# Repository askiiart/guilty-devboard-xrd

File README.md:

# Guilty Devboard Xrd

A dev board for my keyboard, because all the other options kinda suck(ed)

- Compatible with both XIAO nRF52840 Plus and nRF54LM20A
- As efficient as possible
- Fast battery charging (configurable ~50-700mA) and over(dis)charge protection
- Up to 5V 3A from USB, and 3.3V 1A (including MCU power draw)
- 27 GPIO pins, nearly as much as the XIAO nRF54LM20A, despite much more limited manufacturing capabilities, while still having an antenna built-in.

See the documentation for more details on what this has over the official XIAOs.

## Documentation

Docs are available [here](https://askiiart.net/docs/guilty-devboard-xrd.html) ([short link](http://7qq.uk/xrd))

## Note: DRC errors

DRC shows ~140 clearance errors due to the Xiao Plus footprint having pads at and past the edge of the board, a couple things in the keep-out zone, and the QR codes overlapping/being too close to other items. That's intentional, ignore those.

## Schematic

Use Kicanvas to see the [schematic](https://kicanvas.org/?repo=https%3A%2F%2Fgithub.com%2Faskiiart%2Fguilty-devboard-idk%2Fblob%2Fmain%2FPCB%2Fguilty-devboard-idk.kicad_sch)

## Bill of Materials

| Name                           | Quantity needed | MOQ | Price  | Quantity to order | Link                                                                                                              | Total     |
| ------------------------------ | --------------- | --- | ------ | ----------------- | ----------------------------------------------------------------------------------------------------------------- | --------- |
| Diodes                         | 2               | 20  | 0.0257 | 20                | <https://www.lcsc.com/product-detail/C2912031.html>                                                               | 0.514     |
| Ferrite bead                   | 2               | 50  | 0.025  | 50                | <https://www.lcsc.com/product-detail/C525479.html>                                                                | 1.25      |
| MOSFETs                        | 1               | 10  | 0.0434 | 10                | <https://www.lcsc.com/product-detail/C41355091.html>                                                              | 0.434     |
| 100nF cap                      | 5               | 50  | 0.0018 | 50                | <https://www.lcsc.com/product-detail/C2903664.html>                                                               | 0.09      |
| 4.7uF cap                      | 4               | 10  | 0.0733 | 10                | <https://www.lcsc.com/product-detail/C335103.html>                                                                | 0.733     |
| 1pF cap                        | 1               | 100 | 0.0024 | 100               | <https://www.lcsc.com/product-detail/C85894.html>                                                                 | 0.24      |
| 2.2uF cap                      | 2               | 50  | 0.0346 | 50                | <https://www.lcsc.com/product-detail/C335106.html>                                                                | 1.73      |
| 10uF cap                       | 1               | 20  | 0.0368 | 20                | <https://www.lcsc.com/product-detail/C76991.html>                                                                 | 0.736     |
| 1.5pF cap                      | 1               | 100 | 0.003  | 100               | <https://www.lcsc.com/product-detail/C284990.html>                                                                | 0.3       |
| 22uF cap                       | 2               | 5   | 0.1522 | 5                 | <https://www.lcsc.com/product-detail/C7432764.html>                                                               | 0.761     |
| 470nF cap                      | 1               | 100 | 0.0057 | 100               | <https://www.lcsc.com/product-detail/C326573.html>                                                                | 0.57      |
| 1.2pF cap                      | 1               | 100 | 0.0016 | 100               | <https://www.lcsc.com/product-detail/C22374839.html>                                                              | 0.16      |
| 3.3nF inductor                 | 1               | 100 | 0.0073 | 100               | <https://www.lcsc.com/product-detail/C98045.html>                                                                 | 0.73      |
| 1.5uH inductor                 | 1               | 50  | 0.0111 | 50                | <https://www.lcsc.com/product-detail/C2885839.html>                                                               | 0.555     |
| 4.7nH inductor                 | 1               | 100 | 0.0099 | 100               | <https://www.lcsc.com/product-detail/C86126.html>                                                                 | 0.99      |
| 3.6nH inductor                 | 1               | 20  | 0.0322 | 20                | <https://www.lcsc.com/product-detail/C237447.html>                                                                | 0.644     |
| 4.7uH inductor                 | 1               | 1   | 0.2829 | 1                 | <https://www.lcsc.com/product-detail/C7261423.html>                                                               | 0.2829    |
| 1nH inductor                   | 1               | 100 | 0.0029 | 100               | <https://www.lcsc.com/product-detail/C46607389.html>                                                              | 0.29      |
| 5.1k resistor                  | 2               | 100 | 0.0007 | 100               | <https://www.lcsc.com/product-detail/C473460.html>                                                                | 0.07      |
| 470k resistor                  | 1               | 100 | 0.0013 | 100               | <https://www.lcsc.com/product-detail/C54530578.html>                                                              | 0.13      |
| 30 ohm resistor                | 2               | 100 | 0.0008 | 100               | <https://www.lcsc.com/product-detail/C320826.html>                                                                | 0.08      |
| 2k resistor                    | 1               | 100 | 0.0021 | 100               | <https://www.lcsc.com/product-detail/C138107.html>                                                                | 0.21      |
| 1k resistor                    | 1               | 100 | 0.001  | 100               | <https://www.lcsc.com/product-detail/C131396.html>                                                                | 0.1       |
| 806k resistor                  | 1               | 100 | 0.0009 | 100               | <https://www.lcsc.com/product-detail/C474840.html>                                                                | 0.09      |
| 2M resistor                    | 1               | 100 | 0.0006 | 100               | <https://www.lcsc.com/product-detail/C138106.html>                                                                | 0.06      |
| 10k resistor                   | 1               | 100 | 0.001  | 100               | <https://www.lcsc.com/product-detail/C138117.html>                                                                | 0.1       |
| 220k resistor                  | 1               | 100 | 0.003  | 100               | <https://www.lcsc.com/product-detail/C142020.html>                                                                | 0.3       |
| 68k resistor                   | 1               | 100 | 0.003  | 100               | <https://www.lcsc.com/product-detail/C274345.html>                                                                | 0.3       |
| 2.2 ohm resistor               | 1               | 100 | 0.0037 | 100               | <https://www.lcsc.com/product-detail/C473517.html>                                                                | 0.37      |
| 200 ohm resistor               | 1               | 100 | 0.0011 | 100               | <https://www.lcsc.com/product-detail/C304517.html>                                                                | 0.11      |
| SGM40567                       | 1               | 1   | 0.53   | 1                 | <https://www.lcsc.com/product-detail/C5141336.html>                                                               | 0.53      |
| FH9261-G3JH                    | 1               | 20  | 0.0289 | 20                | <https://www.lcsc.com/product-detail/C19273258.html>                                                              | 0.578     |
| BD83070GWL-E2                  | 1               | 1   | 0.7198 | 1                 | <https://www.lcsc.com/product-detail/C2071126.html>                                                               | 0.7198    |
| 32MHz crystal                  | 1               | 5   | 1.0134 | 1                 | <https://www.lcsc.com/product-detail/C5203637.html>                                                               | 1.0134    |
| 32.768kHz crystal              | 1               | 1   | 3.0197 | 1                 | <https://www.lcsc.com/product-detail/C2595065.html>                                                               | 3.0197    |
|                                |                 |     |        |                   |                                                                                                                   |           |
| 2450AT18D0100001E              | 1               | 1   | 0.57   | 1                 | <https://www.digikey.com/en/products/detail/johanson-technology-inc/2450AT18D0100001E/4770685>                    | 0.57      |
|                                |                 |     |        |                   |                                                                                                                   |           |
| NRF54LM20A-QGAA-R              | 1               | 1   | 6.7    | 1                 | <https://mou.sr/44t4RAm>                                                                                          | 6.7       |
| Amphenol 124019772112A (USB-C) | 1               | 1   | 2.41   | 1                 | <https://www.mouser.com/ProductDetail/Amphenol-Commercial-Products/124019772112A?qs=OlC7AqGiEDmvQ2B4jeqfyg%3D%3D> | 2.41      |
|                                |                 |     |        |                   |                                                                                                                   |           |
| JLCPCB                         |                 |     |        |                   |                                                                                                                   | $15.10    |
|                                |                 |     |        |                   |                                                                                                                   |           |
| JLCPCB shipping                |                 |     |        |                   | Roughly                                                                                                           | $9.79     |
| Digikey shipping               |                 |     |        |                   |                                                                                                                   | $4.99     |
| LCSC shipping                  |                 |     |        |                   |                                                                                                                   | 7.25      |
| Mouser shipping                |                 |     |        |                   |                                                                                                                   | 8.49      |
| Mouser estimated tariffs       |                 |     |        |                   |                                                                                                                   | 0.24      |
|                                |                 |     |        |                   |                                                                                                                   |           |
| Subtotal                       |                 |     |        |                   |                                                                                                                   | 74.3308   |
| Total                          |                 |     |        |                   |                                                                                                                   | 80.463091 |

## Notes

- The layer stackup should be JLC0616H-3313, and a stencil with electropolishing is recommended.
- The choice of USB-C connector is odd due to space requirements. If you can find a USB-C connector with the same footprint or smaller - at least in depth - then *please* tell me.
- Kicad, [marbastlib](https://github.com/ebastler/marbastlib), and [nordic-lib-kicad](https://github.com/hlord2000/nordic-lib-kicad) are required for this project.

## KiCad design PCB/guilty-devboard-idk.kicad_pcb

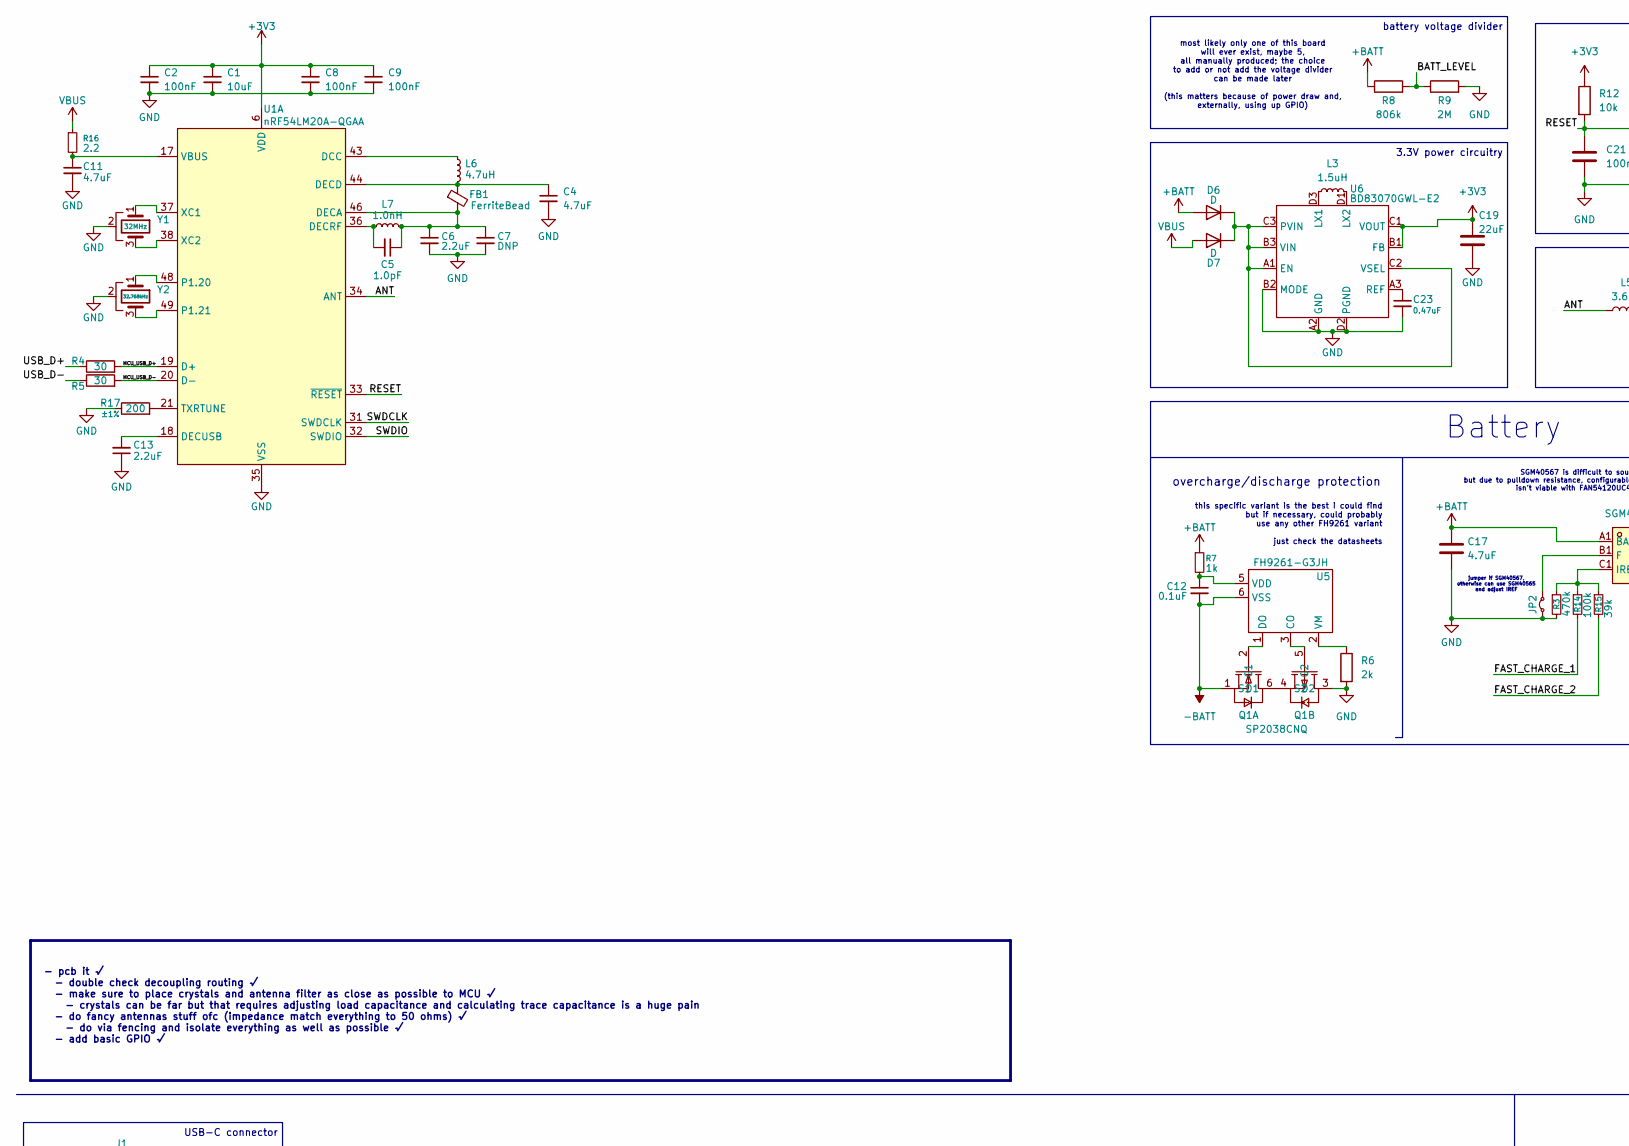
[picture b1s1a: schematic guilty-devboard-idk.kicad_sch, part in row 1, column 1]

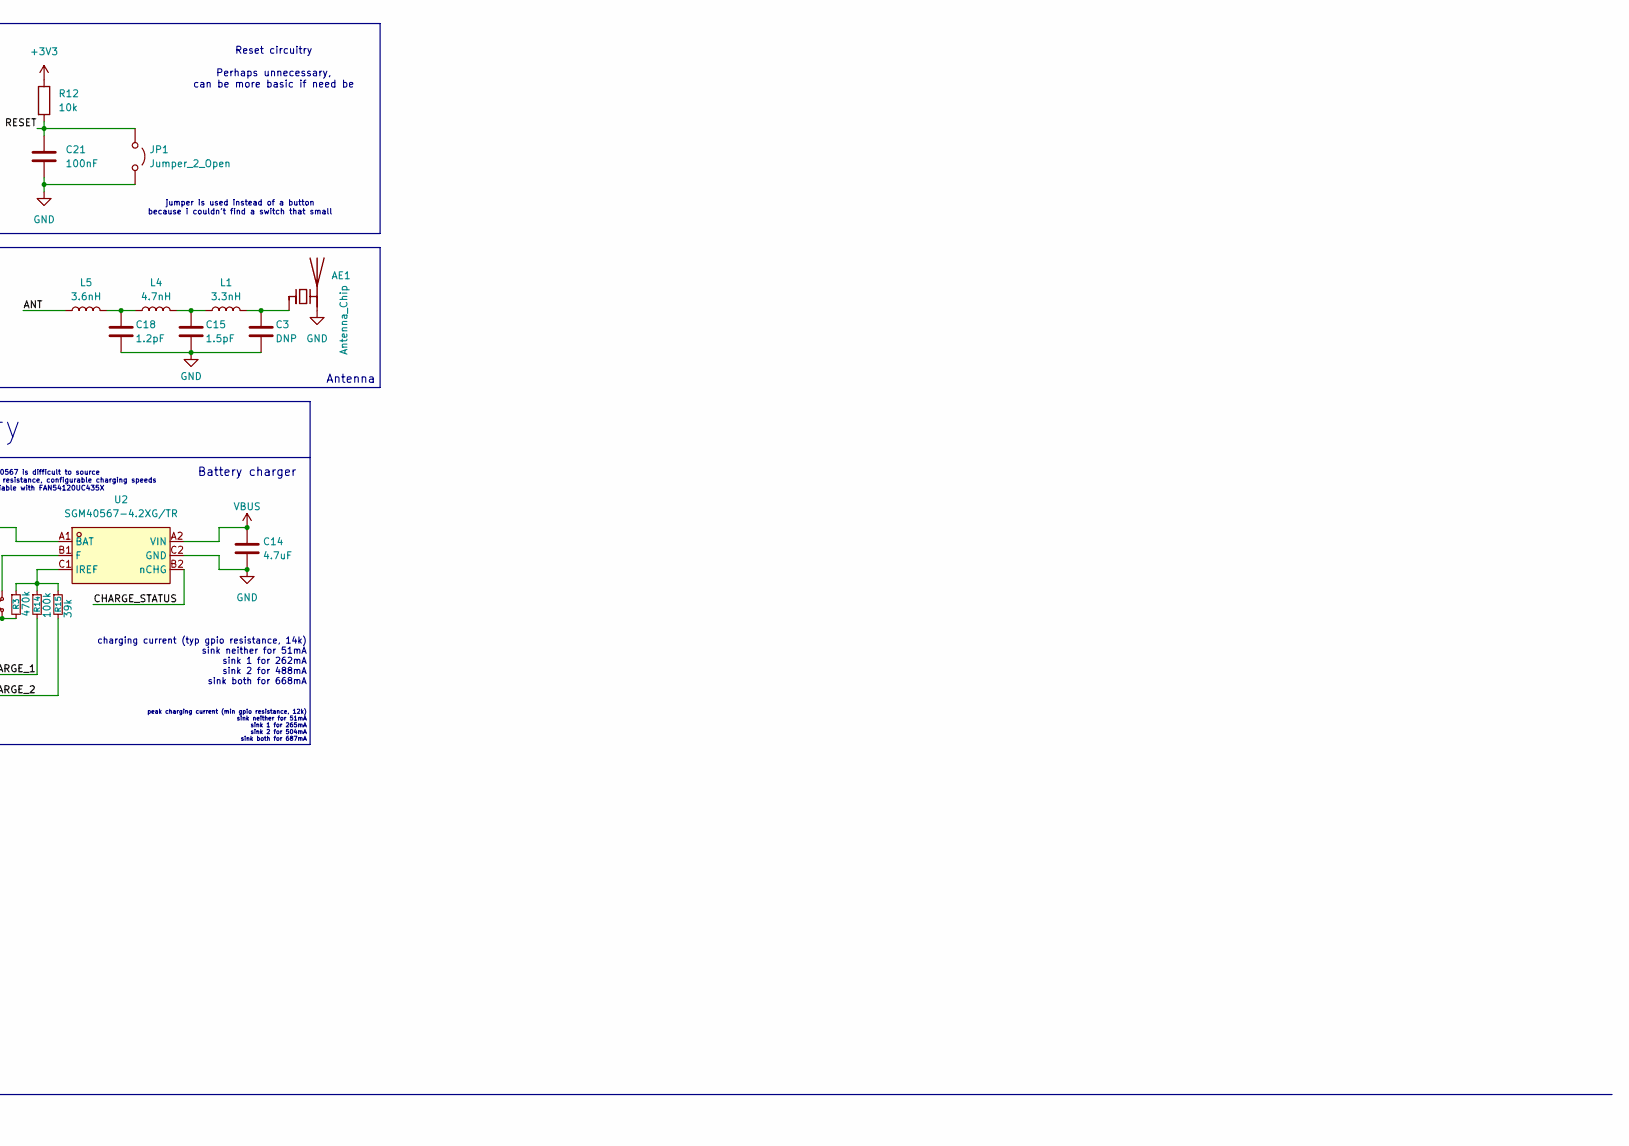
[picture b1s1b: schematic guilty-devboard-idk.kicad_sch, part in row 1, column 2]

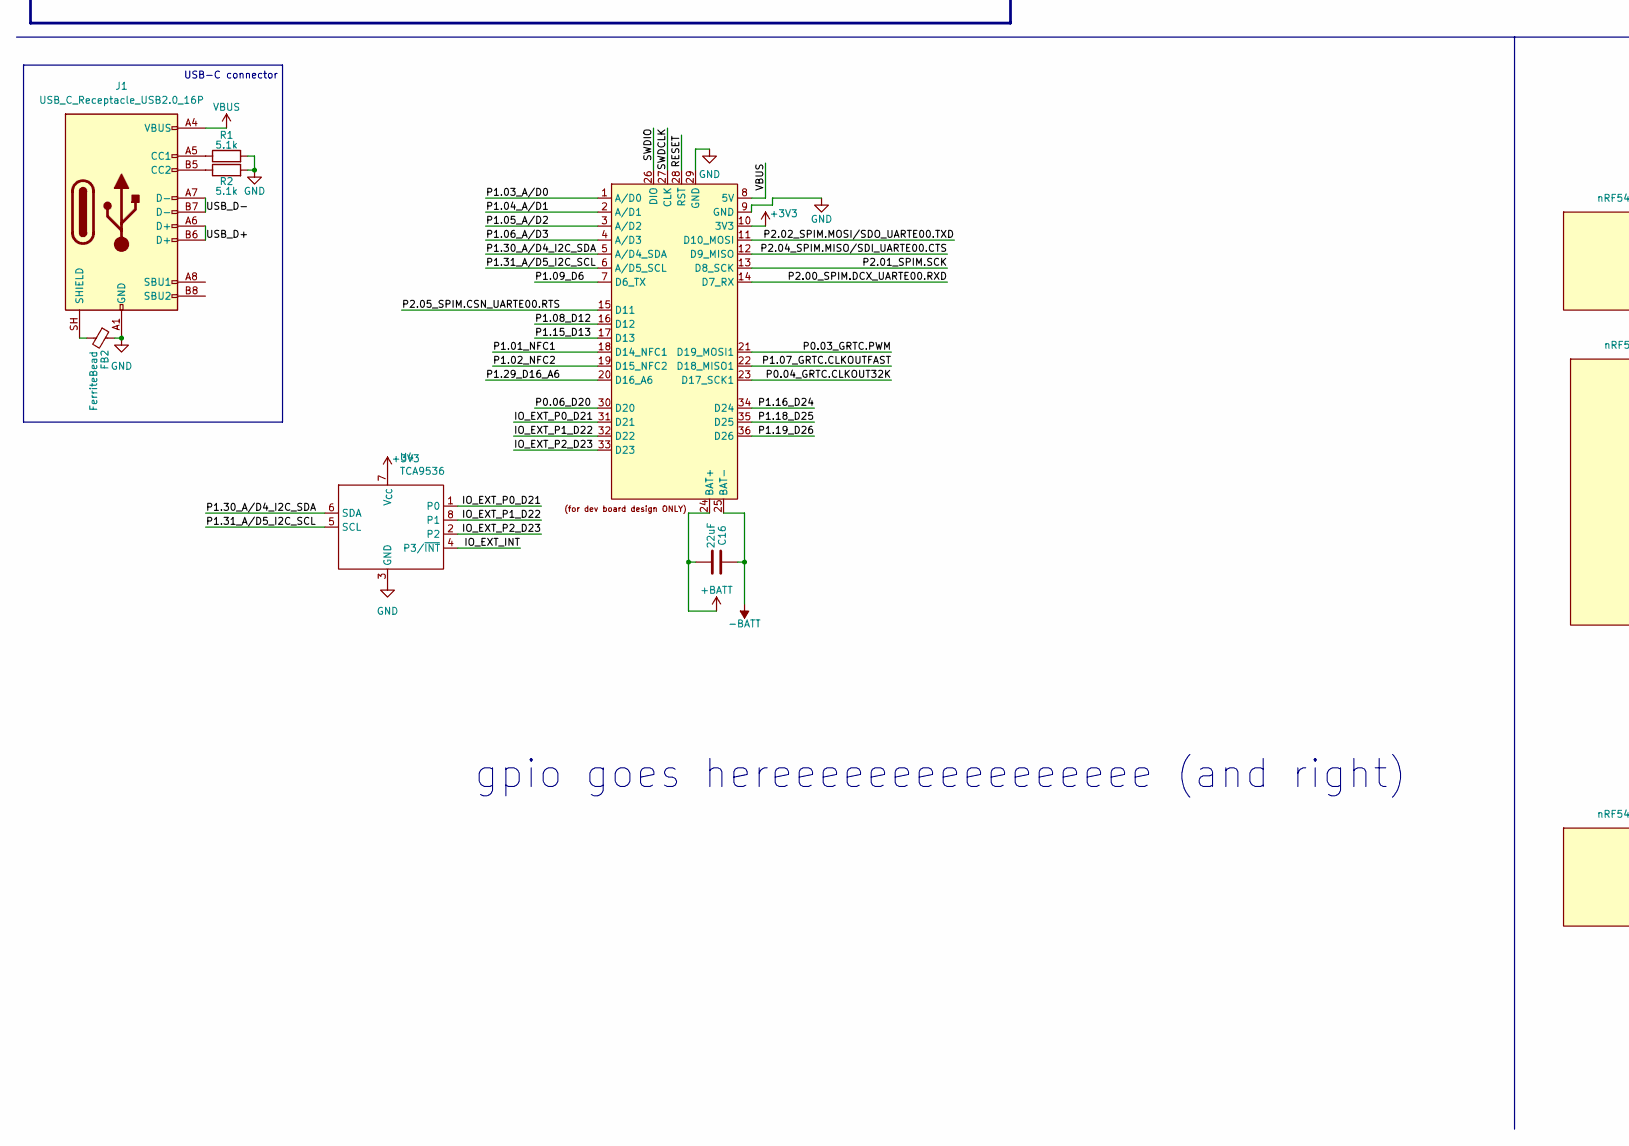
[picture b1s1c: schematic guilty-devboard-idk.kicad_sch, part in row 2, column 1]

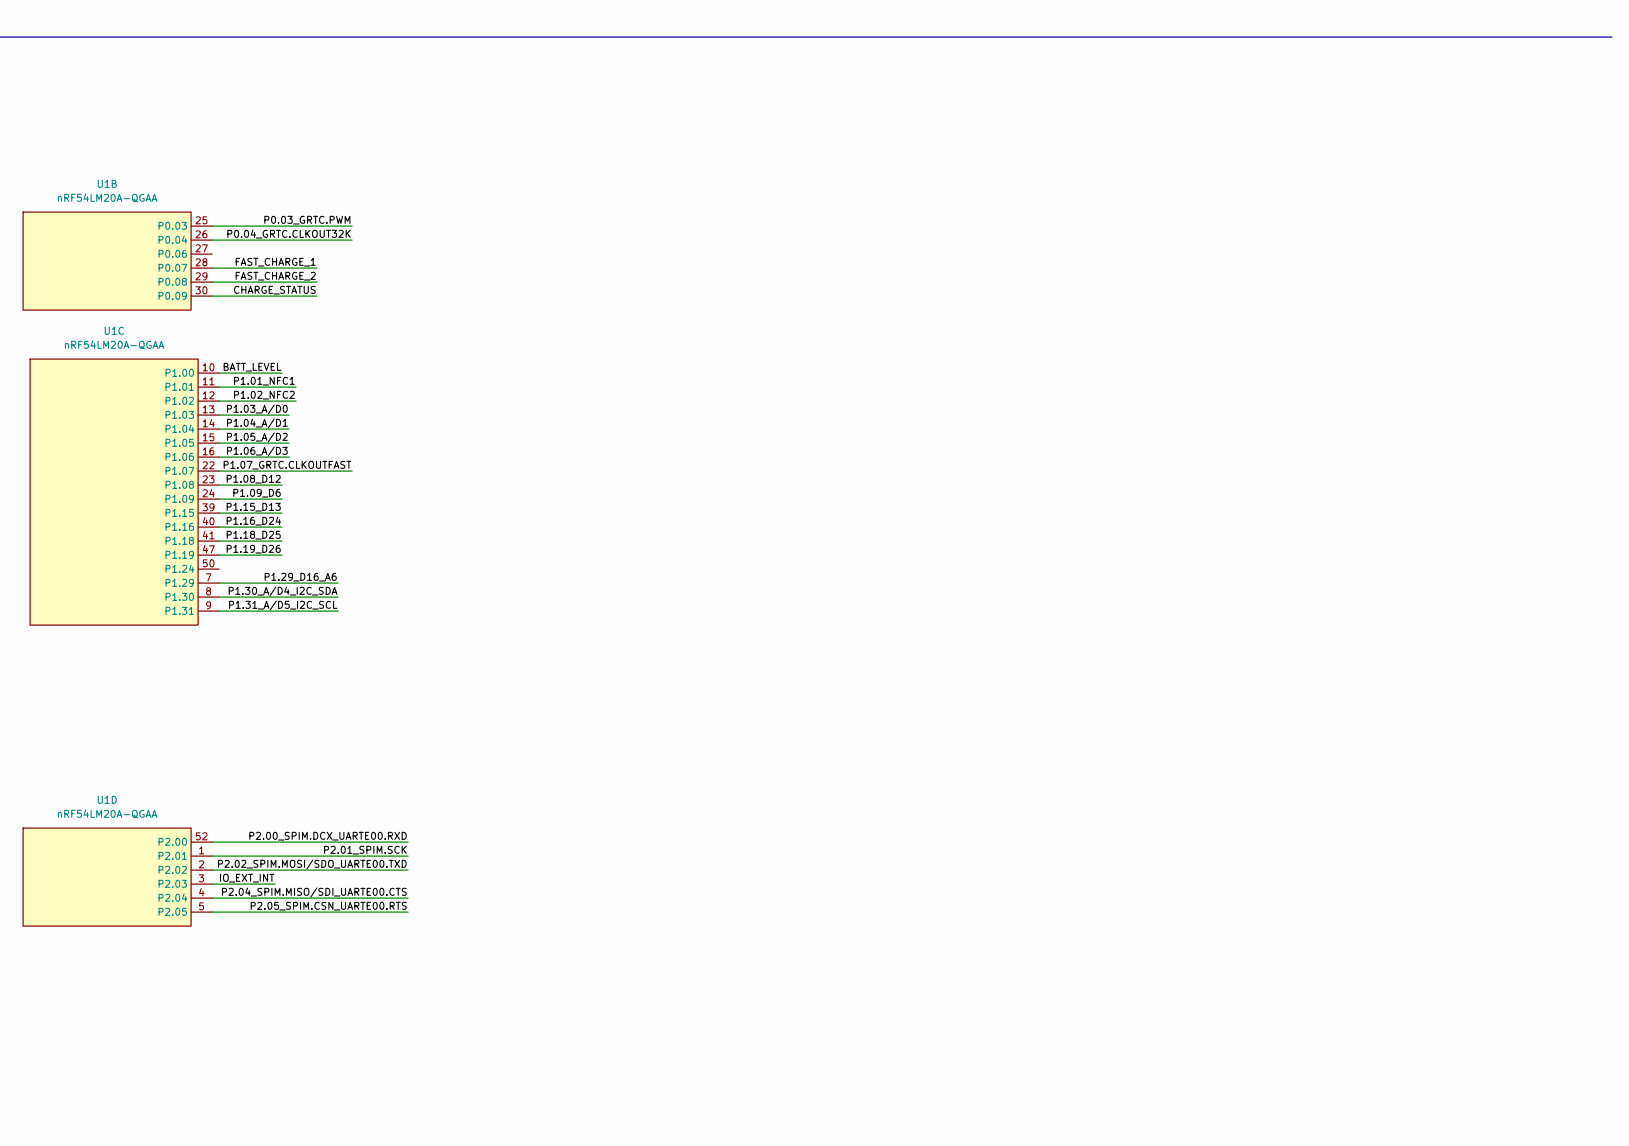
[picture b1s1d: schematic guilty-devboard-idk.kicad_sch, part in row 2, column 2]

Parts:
AE1: Antenna_Chip; 2450AT18D0100001E_L
C1: 10uF; C_0402_1005Metric
C2, C8, C9, C21: 100nF; C_0201_0603Metric
C3, C7: DNP; C_0201_0603Metric
C4, C11, C14, C17: 4.7uF; C_0201_0603Metric
C5: 1.0pF; C_0201_0603Metric
C6, C13: 2.2uF; C_0201_0603Metric
C12: 0.1uF; C_0201_0603Metric
C15: 1.5pF; C_0201_0603Metric
C16, C19: 22uF; C_0402_1005Metric
C18: 1.2pF; C_0201_0603Metric
C23: 0.47uF; C_0201_0603Metric
D6, D7: D; D_SOD-882
FB1, FB2: FerriteBead; L_0201_0603Metric
J1: USB_C_Receptacle_USB2.0_16P; USB_C_Receptacle_Amphenol_124019772112A
JP1: Jumper_2_Open; R_0603_1608Metric
JP2: Jumper_2_Small_Bridged; R_0201_0603Metric
L1: 3.3nH; L_0201_0603Metric
L3: 1.5uH; L_0603_1608Metric
L4: 4.7nH; L_0201_0603Metric
L5: 3.6nH; L_0201_0603Metric
L6: 4.7uH; L_0402_1005Metric
L7: 1.0nH; L_0201_0603Metric
Q1: SP2038CNQ; PDFN-6_L2.0-W2.0-P0.65-BL-EP-1; LCSC Part C41355091
R1, R2: 5.1k; R_0201_0603Metric
R3: 470k; R_0201_0603Metric
R4, R5: 30; R_0201_0603Metric
R6: 2k; R_0201_0603Metric
R7: 1k; R_0201_0603Metric
R8: 806k; R_0201_0603Metric
R9: 2M; R_0201_0603Metric
R12: 10k; R_0201_0603Metric
R14: 100k; R_0201_0603Metric
R15: 39k; R_0201_0603Metric
R16: 2.2; R_0201_0603Metric
R17: 200; R_0201_0603Metric; Tolerance ±1%
U1: nRF54LM20A-QGAA; QFN-52-1EP_6x6mm_P0.4mm_EP4.7x4.7mm_ThermalVias
U2: SGM40567-4.2XG/TR; WLCSP-6_L1.2-W0.9-R3-C2-P0.40-TL; LCSC Part C5141336
U3: Guilty Devboard Xrd pads
U4: TCA9536
U5: FH9261-G3JH; SOT-23-6
U6: BD83070GWL-E2; BD83070GWL
Y1: 32MHz; Crystal_SMD_1210-4Pin_1.2x1.0mm
Y2: 32.768kHz; Crystal_SMD_1210-4Pin_1.2x1.0mm

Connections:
+3V3: C1.1, C2.1, C8.1, C9.1, C19.1, R12.1, U1.6 (VDD), U1.42 (VDD), U1.51 (VDD), U3.10 (3V3), U4.7 (V_{CC}), U6.B1 (FB), U6.C1 (VOUT)
+BATT: C16.2, C17.1, D6.2 (A), R7.1, R8.1, U2.A1 (BAT), U3.24 (BAT+)
-BATT: C12.2, C16.1, Q1.1 (S1), U3.25 (BAT-), U5.6 (VSS)
/ANT: L5.1, U1.34 (ANT)
/BATT_LEVEL: R8.2, R9.1, U1.10 (P1.00)
/CHARGE_STATUS: U1.30 (P0.09), U2.B2 (nCHG)
/FAST_CHARGE_1: R14.2, U1.28 (P0.07)
/FAST_CHARGE_2: R15.2, U1.29 (P0.08)
/IO_EXT_INT: U1.3 (P2.03), U4.4 (P3/~INT)
/IO_EXT_P0_D21: U3.31 (D21), U4.1 (P0)
/IO_EXT_P1_D22: U3.32 (D22), U4.8 (P1)
/IO_EXT_P2_D23: U3.33 (D23), U4.2
/MCU_USB_D+: R4.2, U1.19 (D+)
/MCU_USB_D-: R5.2, U1.20 (D-)
/P0.03_GRTC.PWM: U1.25 (P0.03), U3.21 (D19_MOSI1)
/P0.04_GRTC.CLKOUT32K: U1.26 (P0.04), U3.23 (D17_SCK1)
/P0.06_D20: U3.30 (D20)
/P1.01_NFC1: U1.11 (P1.01), U3.18 (D14_NFC1)
/P1.02_NFC2: U1.12 (P1.02), U3.19 (D15_NFC2)
/P1.03_A/D0: U1.13 (P1.03), U3.1 (A/D0)
/P1.04_A/D1: U1.14 (P1.04), U3.2 (A/D1)
/P1.05_A/D2: U1.15 (P1.05), U3.3 (A/D2)
/P1.06_A/D3: U1.16 (P1.06), U3.4 (A/D3)
/P1.07_GRTC.CLKOUTFAST: U1.22 (P1.07), U3.22 (D18_MISO1)
/P1.08_D12: U1.23 (P1.08), U3.16 (D12)
/P1.09_D6: U1.24 (P1.09), U3.7 (D6_TX)
/P1.15_D13: U1.39 (P1.15), U3.17 (D13)
/P1.16_D24: U1.40 (P1.16), U3.34 (D24)
/P1.18_D25: U1.41 (P1.18), U3.35 (D25)
/P1.19_D26: U1.47 (P1.19), U3.36 (D26)
/P1.29_D16_A6: U1.7 (P1.29), U3.20 (D16_A6)
/P1.30_A/D4_I2C_SDA: U1.8 (P1.30), U3.5 (A/D4_SDA), U4.6 (SDA)
/P1.31_A/D5_I2C_SCL: U1.9 (P1.31), U3.6 (A/D5_SCL), U4.5 (SCL)
/P2.00_SPIM.DCX_UARTE00.RXD: U1.52 (P2.00), U3.14 (D7_RX)
/P2.01_SPIM.SCK: U1.1 (P2.01), U3.13 (D8_SCK)
/P2.02_SPIM.MOSI/SDO_UARTE00.TXD: U1.2 (P2.02), U3.11 (D10_MOSI)
/P2.04_SPIM.MISO/SDI_UARTE00.CTS: U1.4 (P2.04), U3.12 (D9_MISO)
/P2.05_SPIM.CSN_UARTE00.RTS: U1.5 (P2.05), U3.15 (D11)
/RESET: C21.1, JP1.1 (A), R12.2, U1.33 (~RESET), U3.28 (RST)
/SWDCLK: U1.31 (SWDCLK), U3.27 (CLK)
/SWDIO: U1.32 (SWDIO), U3.26 (DIO)
/USB_D+: J1.A6 (D+), J1.B6 (D+), R4.1
/USB_D-: J1.A7 (D-), J1.B7 (D-), R5.1
GND: AE1.2 (PCB_Trace), C1.2, C2.2, C3.1, C4.2, C6.2, C7.2, C8.2, C9.2, C11.2, C13.1, C14.2, C15.1, C17.2, C18.1, C19.2, C21.2, C23.2, FB2.1, J1.A1 (GND), J1.A12 (GND), J1.B1 (GND), J1.B12 (GND), JP1.2 (B), JP2.1 (A), Q1.3 (D2), R1.2, R2.2, R3.2, R6.2, R9.2, R17.1, U1.35 (VSS), U1.45 (VSS), U1.53 (VSS), U2.C2 (GND), U3.9 (GND), U3.29 (GND), U4.3 (GND), U6.A2 (GND), U6.B2 (MODE), U6.D2 (PGND), Y1.2, Y2.2
unnamed: AE1.1 (FEED), C3.2, L1.2
unnamed: C15.2, L1.1, L4.2
unnamed: C18.2, L4.1, L5.2
unnamed: D6.1 (K), D7.1 (K), U6.A1 (EN), U6.B3 (VIN), U6.C2 (VSEL), U6.C3 (PVIN)
unnamed: J1.A5 (CC1), R1.1
unnamed: J1.B5 (CC2), R2.1
unnamed: FB2.2, J1.SH (SHIELD)
unnamed: JP2.2 (B), U2.B1 (F)
unnamed: Q1.4 (S2), Q1.6 (D1)
unnamed: Q1.2 (G1), U5.1 (DO)
unnamed: Q1.5 (G2), U5.3 (CO)
unnamed: L6.1, U1.43 (DCC)
unnamed: C5.1, C6.1, C7.1, FB1.2, L7.2, U1.46 (DECA)
unnamed: C4.1, FB1.1, L6.2, U1.44 (DECD)
unnamed: C5.2, L7.1, U1.36 (DECRF)
unnamed: C13.2, U1.18 (DECUSB)
unnamed: U1.48 (P1.20), Y2.1
unnamed: U1.49 (P1.21), Y2.3
unnamed: R17.2, U1.21 (TXRTUNE)
unnamed: C11.1, R16.2, U1.17 (VBUS)
unnamed: U1.37 (XC1), Y1.1
unnamed: U1.38 (XC2), Y1.3
unnamed: R3.1, R14.1, R15.1, U2.C1 (IREF)
unnamed: C12.1, R7.2, U5.5 (VDD)
unnamed: R6.1, U5.2 (VM)
unnamed: L3.1, U6.D3 (LX1)
unnamed: L3.2, U6.D1 (LX2)
unnamed: C23.1, U6.A3 (REF)
VBUS: C14.1, D7.2 (A), J1.A4 (VBUS), J1.A9 (VBUS), J1.B4 (VBUS), J1.B9 (VBUS), R16.1, U2.A2 (VIN), U3.8 (5V)

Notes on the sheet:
charging current (typ gpio resistance, 14k) sink neither for 51mA sink 1 for 262mA sink 2 for 488mA sink both for 668mA
Reset circuitry Perhaps unnecessary, can be more basic if need be
Battery charger
battery voltage divider
- pcb it √ - double check decoupling routing √ - make sure to place crystals and antenna filter as close as possible to MCU √ - crystals can be far but that requires adjusting load capacitance and calculating trace capacitance is a huge pain - do fancy antennas stuff ofc (impedance match everything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
SGM40567 is difficult to source but due to pulldown resistance, configurable charging speeds isn't viable with FAN54120UC435X
jumper is used instead of a button because i couldn't find a switch that small
this specific variant is the best i could find but if necessary, could probably use any other FH9261 variant just check the datasheets
Antenna
USB-C connector
gpio goes hereeeeeeeeeeeeeeee (and right)
Battery
overcharge/discharge protection
3.3V power circuitry
jumper if SGM40567, otherwise can use SGM40565 and adjust IREF
peak charging current (min gpio resistance, 12k) sink neither for 51mA sink 1 for 265mA sink 2 for 504mA sink both for 687mA
most likely only one of this board will ever exist, maybe 5, all manually produced; the choice to add or not add the voltage divider can be made later (this matters because of power draw and, externally, using up GPIO)

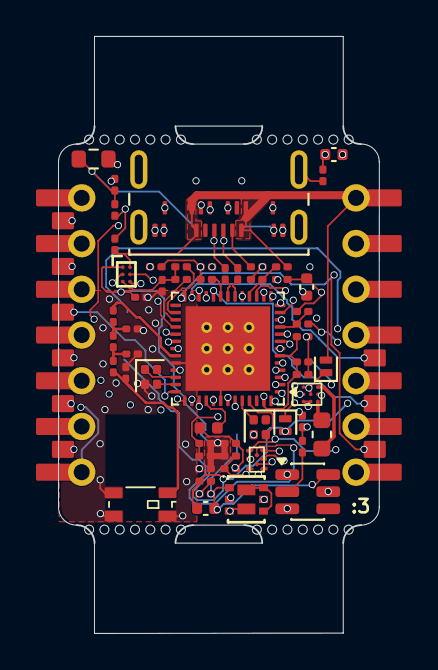
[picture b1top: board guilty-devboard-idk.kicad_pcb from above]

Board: 6 copper layers, 17.8 x 33.2 mm, 57 parts (0 on the bottom side), 72 nets.

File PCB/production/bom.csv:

Designator,Footprint,Quantity,Value,LCSC Part #
AE1,2450AT18D0100001E_L,1,Antenna_Chip,
C1,0402,1,10uF,
"C11, C14, C17, C4",0201,4,4.7uF,
C12,0201,1,0.1uF,
"C13, C6",0201,2,2.2uF,
C15,0201,1,1.5pF,
"C16, C19",0402,2,22uF,
C18,0201,1,1.2pF,
"C2, C21, C8, C9",0201,4,100nF,
C23,0201,1,0.47uF,
"C3, C7",0201,2,DNP,
C5,0201,1,1.0pF,
"D6, D7",D_SOD-882,2,D,
"FB1, FB2",0201,2,FerriteBead,
J1,USB_C_Receptacle_Amphenol_124019772112A,1,USB_C_Receptacle_USB2.0_16P,
JP1,0603,1,Jumper_2_Open,
L1,0201,1,3.3nH,
L3,0603,1,1.5uH,
L4,0201,1,4.7nH,
L5,0201,1,3.6nH,
L6,0402,1,4.7uH,
L7,0201,1,1.0nH,
Q1,PDFN-6_L2.0-W2.0-P0.65-BL-EP-1,1,SP2038CNQ,C41355091
"R1, R2",0201,2,5.1k,
R12,0201,1,10k,
R14,0201,1,220k,
R15,0201,1,68k,
R16,0201,1,2.2,
R17,0201,1,200,
R3,0201,1,470k,
"R4, R5",0201,2,30,
R6,0201,1,2k,
R7,0201,1,1k,
R8,0201,1,806k,
R9,0201,1,2M,
U1,QFN-52-1EP_6x6mm_P0.4mm_EP4.7x4.7mm_ThermalVias,1,nRF54LM20A-QGAA,
U2,WLCSP-6_L1.2-W0.9-R3-C2-P0.40-TL,1,SGM40567-4.2XG/TR,C5141336
U4,TCA9536,1,TCA9536,
U5,SOT-23-6,1,FH9261-G3JH,
U6,BD83070GWL,1,BD83070GWL-E2,
Y1,Crystal_SMD_1210-4Pin_1.2x1.0mm,1,32MHz,
Y2,Crystal_SMD_1210-4Pin_1.2x1.0mm,1,32.768kHz,

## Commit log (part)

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2026-05-04 commit idk pre-10.0 update
2026-05-20 idk pretty much finish schematic everything should be right, besides adding more basic gpio when convenient
2026-05-22 add README
2026-05-25 terrible half done routing idk - post-decent filter routing
2026-05-27 fully routed
2026-05-27 update readme yet again
2026-05-28 update routing to make antenna better
2026-06-04 update readme a bit
2026-06-05 add lib for stuff using this
2026-06-06 improve via fencing and make it slightly longer for tolerance
2026-06-14 misc notes and whatnot on schematic, got rid of unnecessary via/GNDed pin
2026-06-21 update readme with prod info
2026-06-22 add 5mm edges for pcba
2026-06-24 add BOM
